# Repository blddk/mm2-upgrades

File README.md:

This is made for holding files, mostly for my MM2 upgrades.

You can find the upgrades here: http://captain-slow.dk/category/reprap/mendelmax-2/

All my designs are released under the SA 2.0 license http://creativecommons.org/licenses/by-sa/2.0/

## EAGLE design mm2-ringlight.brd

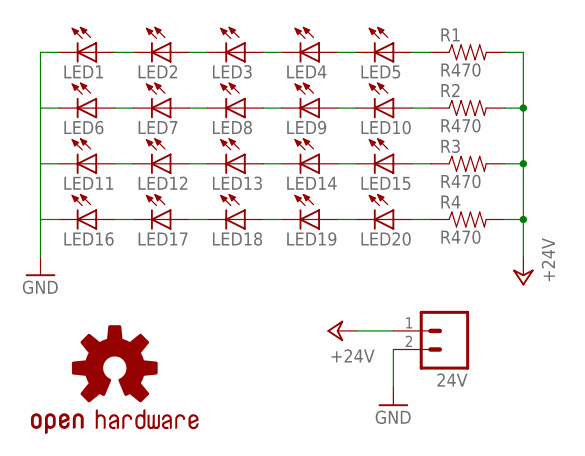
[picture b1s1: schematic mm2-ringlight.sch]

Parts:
24V: M02PTH; 1X02
LED1, LED2, LED3, LED4, LED5, LED6, LED7, LED8, LED9, LED10, LED11, LED12, LED13, LED14, LED15, LED16, LED17, LED18, LED19, LED20: LEDCHIPLED_0805; CHIPLED_0805
R1, R2, R3, R4: R470; 0805
U$1: OSHW-LOGOS; OSHW-LOGO-S

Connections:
+24V: 24V.1, R1.2, R2.2, R3.2, R4.2
GND: 24V.2, LED1.C, LED6.C, LED11.C, LED16.C
unnamed: LED5.A, R1.1
unnamed: LED16.A, LED17.C
unnamed: LED17.A, LED18.C
unnamed: LED18.A, LED19.C
unnamed: LED19.A, LED20.C
unnamed: LED14.A, LED15.C
unnamed: LED13.A, LED14.C
unnamed: LED12.A, LED13.C
unnamed: LED11.A, LED12.C
unnamed: LED6.A, LED7.C
unnamed: LED7.A, LED8.C
unnamed: LED8.A, LED9.C
unnamed: LED9.A, LED10.C
unnamed: LED4.A, LED5.C
unnamed: LED3.A, LED4.C
unnamed: LED2.A, LED3.C
unnamed: LED1.A, LED2.C
unnamed: LED10.A, R2.1
unnamed: LED15.A, R3.1
unnamed: LED20.A, R4.1

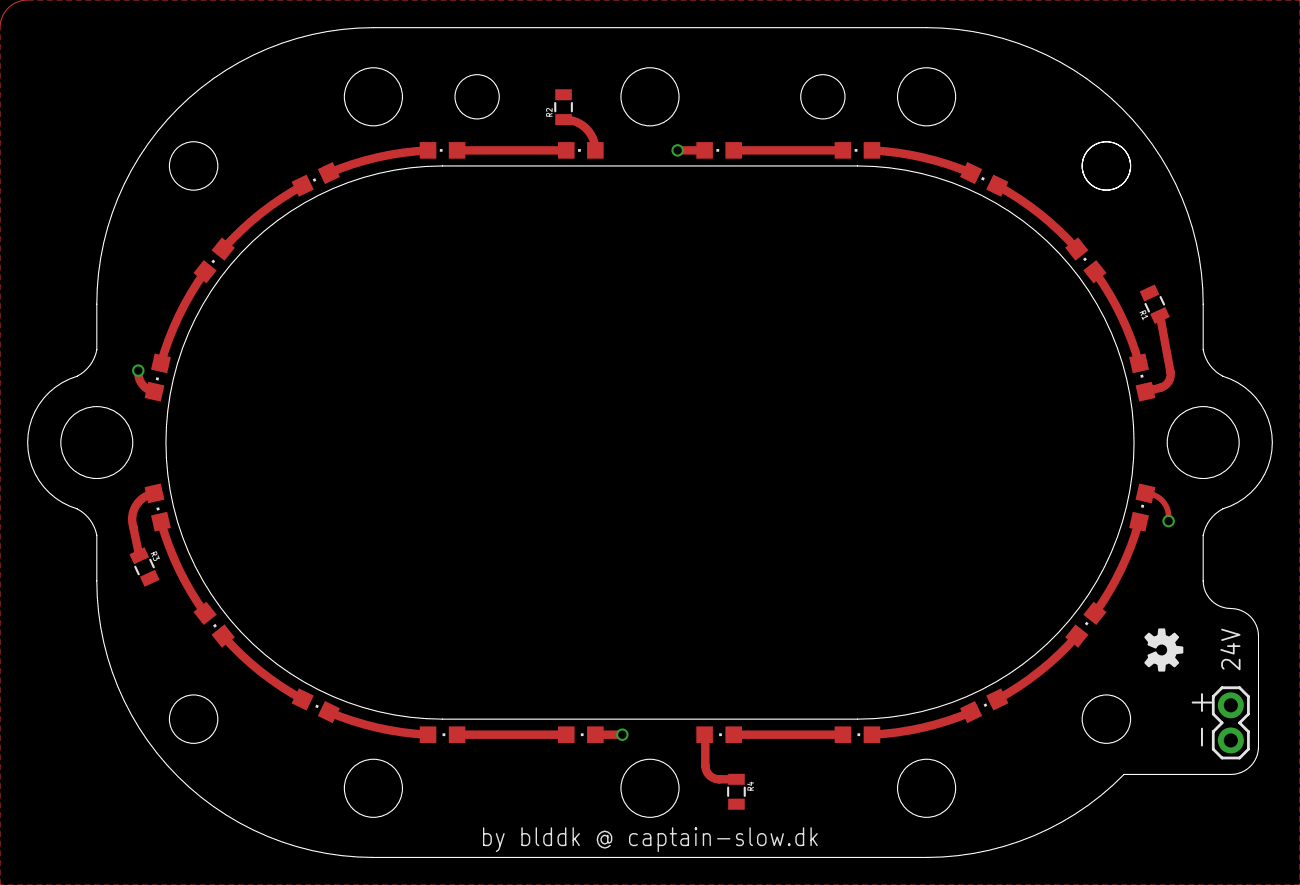
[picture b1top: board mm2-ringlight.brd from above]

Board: 2 copper layers, 90.0 x 60.0 mm, 26 parts (0 on the bottom side), 22 nets.

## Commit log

2013-07-19 initial
2013-07-21 Initial uploa
2013-07-21 Revert "Initial uploa"
    This reverts commit 5c943ae6ca513f41a1a179496813e4f22d3787f2.
2013-07-21 Create README.md
    This is made for holding files, mostly for my MM2 upgrades.
    You can find the upgrades here: http://captain-slow.dk/category/reprap/mendelmax-2/
2013-08-05 Init

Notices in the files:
parts and their libraries:
SparkFun: Licensing: CC v3.0 Share-Alike You are welcome to use this library for commercial purposes.
